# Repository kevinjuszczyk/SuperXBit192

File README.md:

# SuperXBit192
 Lo-fi handheld gaming

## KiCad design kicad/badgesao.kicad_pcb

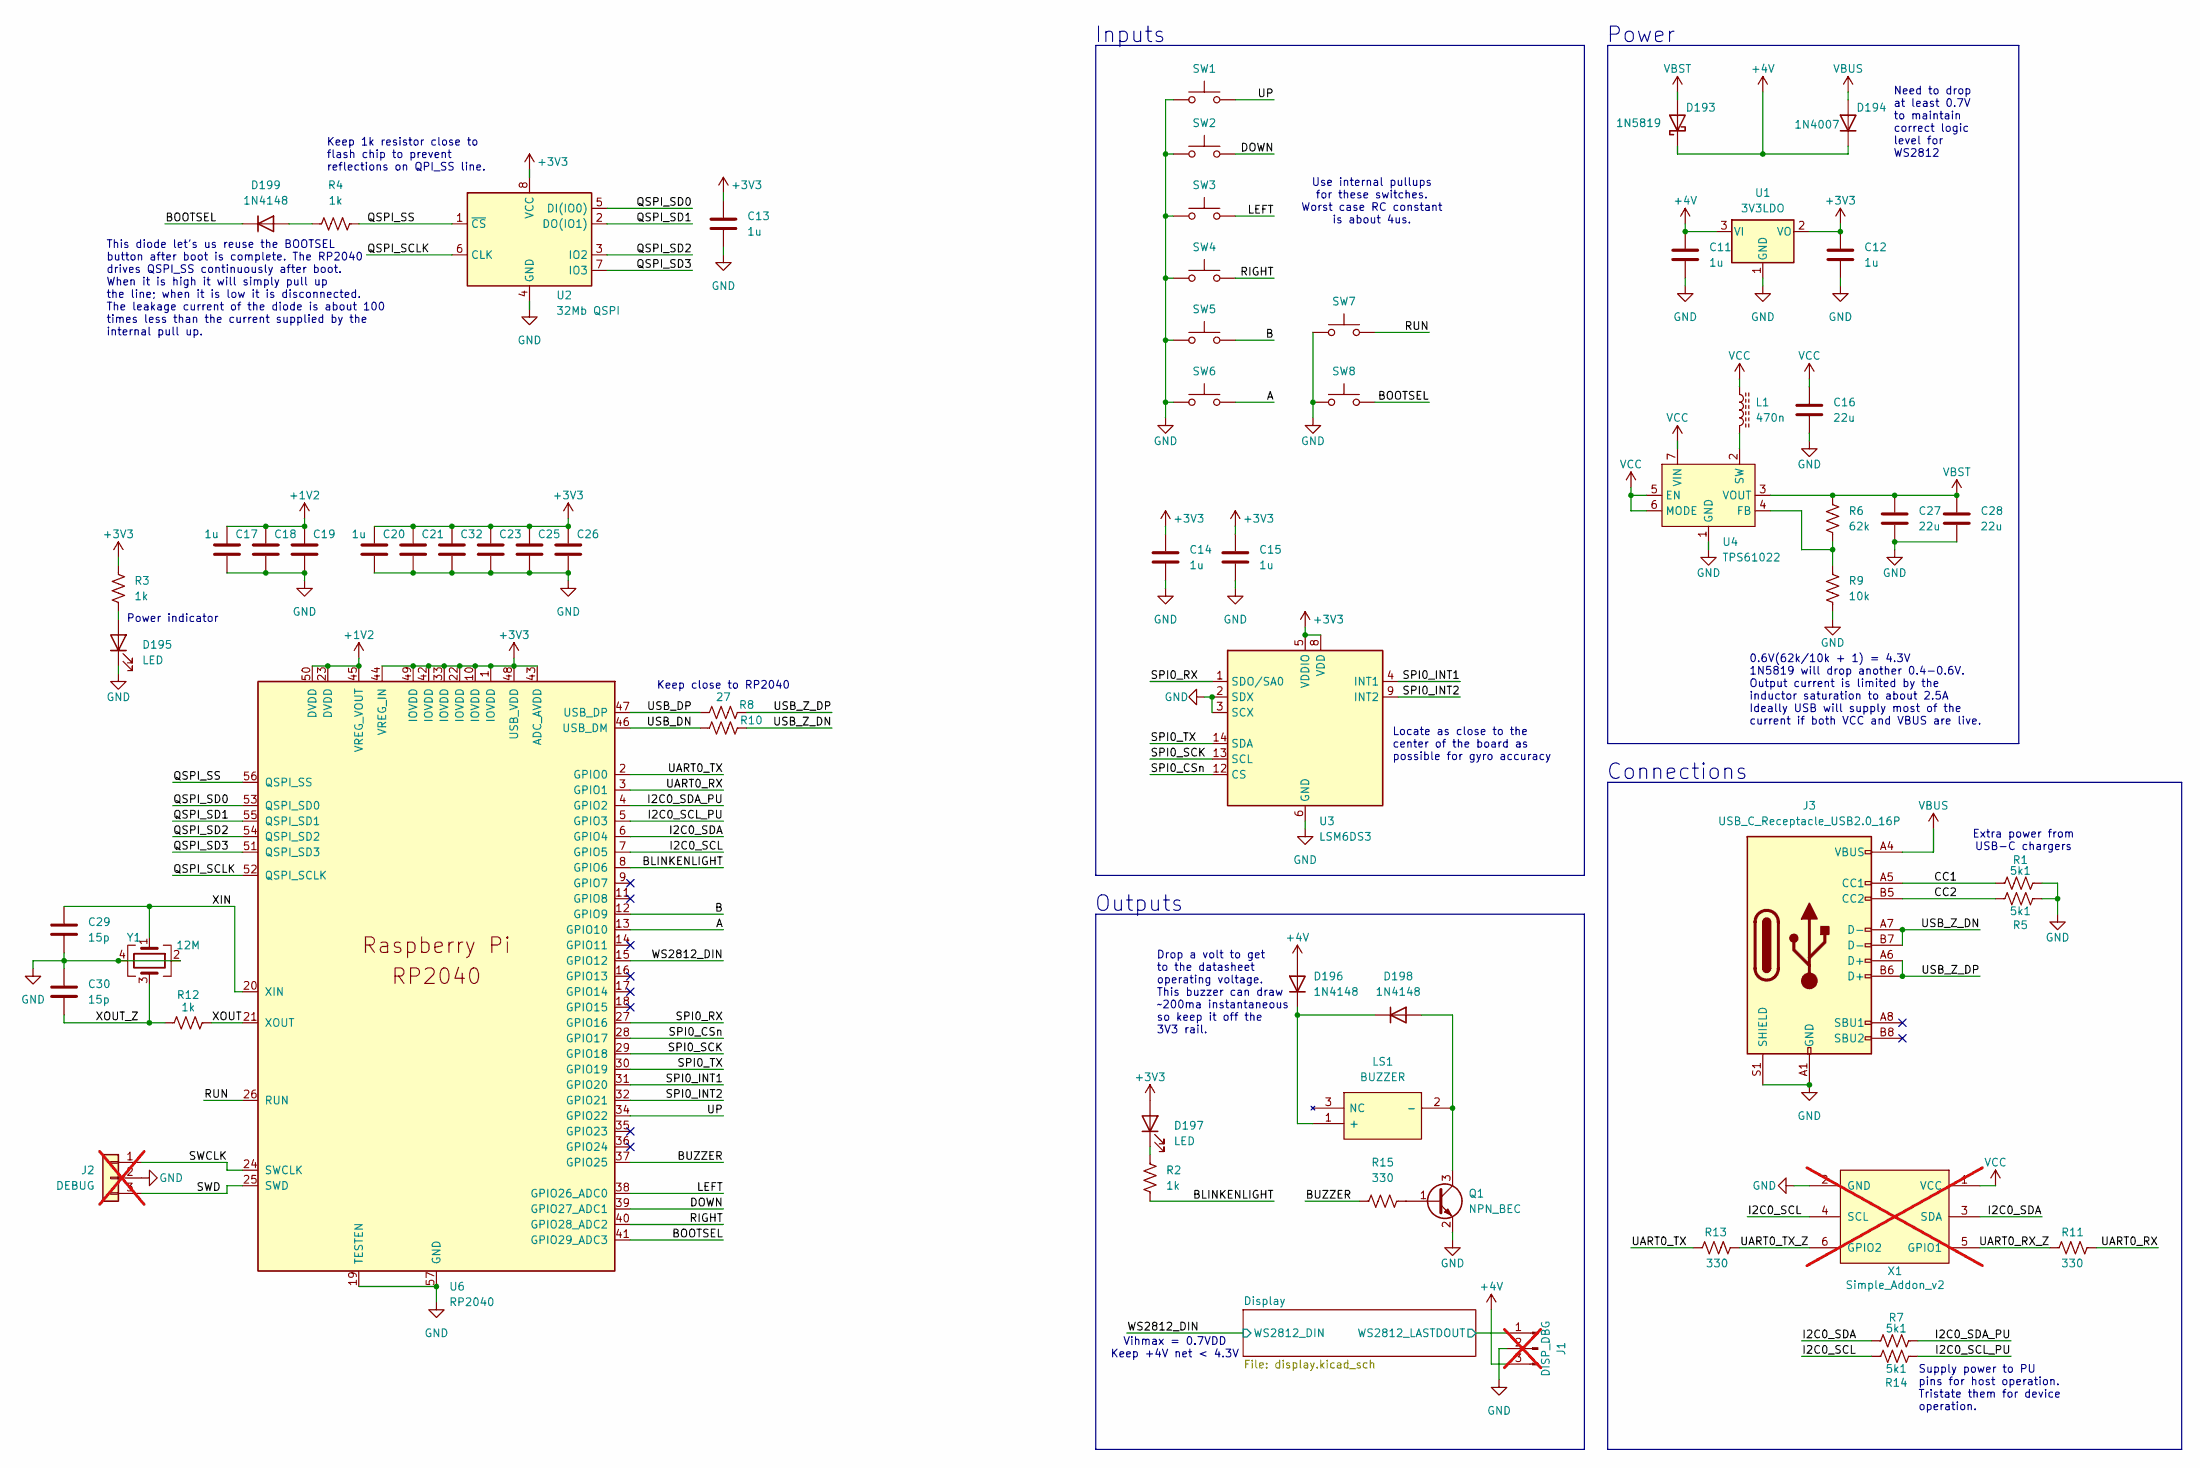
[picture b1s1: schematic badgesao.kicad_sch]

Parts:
C11, C12, C13, C14, C15, C17, C18, C19, C20, C21, C23, C25, C26, C32: 1u; C_0402_1005Metric; Manufacturer_Part_Number CL05A105KA5NQNC; LCSC C52923
C16, C27, C28: 22u; C_0805_2012Metric; Manufacturer_Part_Number CL21A226MAQNNNE; LCSC C45783
C29, C30: 15p; C_0402_1005Metric; Manufacturer_Part_Number 0402CG150J500NT; LCSC C1548
D193: 1N5819; D_SOD-323; Manufacturer_Part_Number 1N5819WS; LCSC C191023
D194: 1N4007; D_SOD-123F; Manufacturer_Part_Number SM4007PL; LCSC C64898
D195, D197: LED; D_0603_1608Metric; Manufacturer_Part_Number KT-0603R; LCSC C2286
D196, D198, D199: 1N4148; D_SOD-523; Manufacturer_Part_Number 1N4148WT; LCSC C7420320
J1: DISP_DBG; PinHeader_1x03_P1.27mm_Vertical; Manufacturer_Part_Number M50-3530342; Digikey_Part 952-3599-ND; not fitted
J2: DEBUG; PinHeader_1x03_P2.54mm_Vertical; Manufacturer_Part_Number 61300311121; Digikey_Part 732-5316-ND; not fitted
J3: USB_C_Receptacle_USB2.0_16P; USB_C_Receptacle_GCT_USB4105-xx-A_16P_TopMnt_Horizontal; Manufacturer_Part_Number U263-163N-4BLS1735; LCSC C2931474
L1: 470n; L_1008_2520Metric; Manufacturer_Part_Number 1239AS-H-R47M=P2; LCSC C576393
LS1: BUZZER; CMT5023SSMTTR; Manufacturer_Part_Number FUET-5020; LCSC C391029
Q1: NPN_BEC; SOT-323_SC-70; Manufacturer_Part_Number MMST3904; LCSC C22388837
R1, R5, R7, R14: 5k1; R_0402_1005Metric; Manufacturer_Part_Number 0402WGF5101TCE; LCSC C25905
R2, R3, R4, R12: 1k; R_0402_1005Metric; Manufacturer_Part_Number 0402WGF1001TCE; LCSC C11702
R6: 62k; R_0402_1005Metric; Manufacturer_Part_Number FRC0402J623TS; LCSC C2929930
R8, R10: 27; R_0402_1005Metric; Manufacturer_Part_Number 0402WGF330JTCE; LCSC C25105
R9: 10k; R_0402_1005Metric; Manufacturer_Part_Number 0402WGF1002TCE; LCSC C25744
R11, R13, R15: 330; R_0402_1005Metric; Manufacturer_Part_Number 0402WGF3300TCE; LCSC C25104
SW1: UP; SW_SPST_PTS810; Manufacturer_Part_Number PTS810SJM250SMTRLFS; LCSC C116501
SW2: DOWN; SW_SPST_PTS810; Manufacturer_Part_Number PTS810SJM250SMTRLFS; LCSC C116501
SW3: LEFT; SW_SPST_PTS810; Manufacturer_Part_Number PTS810SJM250SMTRLFS; LCSC C116501
SW4: RIGHT; SW_SPST_PTS810; Manufacturer_Part_Number PTS810SJM250SMTRLFS; LCSC C116501
SW5: B; SW_SPST_PTS810; Manufacturer_Part_Number PTS810SJM250SMTRLFS; LCSC C116501
SW6: A; SW_SPST_PTS810; Manufacturer_Part_Number PTS810SJM250SMTRLFS; LCSC C116501
SW7: RESET; PTS830GM140SMTRLFS; Manufacturer_Part_Number PTS830GG140SMTRLFS; LCSC C221902
SW8: BOOTSEL; PTS830GM140SMTRLFS; Manufacturer_Part_Number PTS830GG140SMTRLFS; LCSC C221902
U1: 3V3LDO; SOT-23; Manufacturer_Part_Number XC6206P332MR-G; LCSC C5446
U2: 32Mb QSPI; Winbond_USON-8-1EP_3x2mm_P0.5mm_EP0.2x1.6mm; Manufacturer_Part_Number ZD25WQ32CEIGR; LCSC C5258281
U3: LSM6DS3; LGA-14_3x2.5mm_P0.5mm_LayoutBorder3x4y; Manufacturer_Part_Number LSM6DS3TR; LCSC C95230
U4: TPS61022; Texas_RWU0007A_VQFN-7_2x2mm_P0.5mm; Manufacturer_Part_Number TPS61022RWUR; LCSC C915088
U6: RP2040; QFN-56-1EP_7x7mm_P0.4mm_EP3.2x3.2mm; Manufacturer_Part_Number RP2040; LCSC C2040
X1: Simple_Addon_v2; Simple_Addon_v2-SAO-2x3; Manufacturer_Part_Number 75869-131LF; Digikey_Part 609-2845-ND; not fitted
Y1: 12M; Crystal_SMD_SeikoEpson_FA238-4Pin_3.2x2.5mm; Manufacturer_Part_Number X322512MSB4SI; LCSC C9002

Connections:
+1V2: C17.1, C18.1, C19.1, U6.23 (DVDD), U6.45 (VREG_VOUT), U6.50 (DVDD)
+4V: C11.1, D193.1 (K), D194.1 (K), D196.2 (A), J1.3, U1.3 (VI); also elsewhere on the board
/A: SW6.2, U6.13 (GPIO10)
/B: SW5.2, U6.12 (GPIO9)
/BLINKENLIGHT: R2.1, U6.8 (GPIO6)
/CC1: J3.A5 (CC1), R1.2
/CC2: J3.B5 (CC2), R5.2
/Display/WS2812_LASTDOUT: J1.1; also elsewhere on the board
/I2C0_SCL: R14.2, U6.7 (GPIO5), X1.4 (SCL)
/I2C0_SCL_PU: R14.1, U6.5 (GPIO3)
/I2C0_SDA: R7.2, U6.6 (GPIO4), X1.3 (SDA)
/I2C0_SDA_PU: R7.1, U6.4 (GPIO2)
/QSPI_SCLK: U2.6 (CLK), U6.52 (QSPI_SCLK)
/QSPI_SD0: U2.5 (DI(IO0)), U6.53 (QSPI_SD0)
/QSPI_SD1: U2.2 (DO(IO1)), U6.55 (QSPI_SD1)
/QSPI_SD2: U2.3 (IO2), U6.54 (QSPI_SD2)
/QSPI_SD3: U2.7 (IO3), U6.51 (QSPI_SD3)
/QSPI_SS: R4.1, U2.1 (~CS), U6.56 (QSPI_SS)
/RUN: SW7.2, U6.26 (RUN)
/SWCLK: J2.1, U6.24 (SWCLK)
/SWD: J2.3, U6.25 (SWD)
/UART0_RX: R11.2, U6.3 (GPIO1)
/UART0_RX_Z: R11.1, X1.5 (GPIO1)
/UART0_TX: R13.1, U6.2 (GPIO0)
/UART0_TX_Z: R13.2, X1.6 (GPIO2)
/USB_DN: R10.2, U6.46 (USB_DM)
/USB_DP: R8.2, U6.47 (USB_DP)
/USB_Z_DN: J3.A7 (D-), J3.B7 (D-), R10.1
/USB_Z_DP: J3.A6 (D+), J3.B6 (D+), R8.1
/WS2812_DIN: U6.15 (GPIO12); also elsewhere on the board
/XIN: C29.1, U6.20 (XIN), Y1.1
/XOUT: R12.1, U6.21 (XOUT)
/XOUT_Z: C30.2, R12.2, Y1.3
unnamed: D195.2 (A), R3.1
unnamed: D196.1 (K), D198.1 (K), LS1.1 (+)
unnamed: D197.1 (K), R2.2
unnamed: D198.2 (A), LS1.2 (-), Q1.3 (C)
unnamed: D199.2 (A), R4.2
unnamed: Q1.1 (B), R15.1
unnamed: R6.2, R9.1, U4.4 (FB)
unnamed: L1.2, U4.2 (SW)
VBST: C27.1, C28.1, D193.2 (A), R6.1, U4.3 (VOUT)
VBUS: D194.2 (A), J3.A4 (VBUS), J3.A9 (VBUS), J3.B4 (VBUS), J3.B9 (VBUS)
VCC: C16.1, L1.1, U4.5 (EN), U4.6 (MODE), U4.7 (VIN), X1.1 (VCC)

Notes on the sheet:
This diode let's us reuse the BOOTSEL button after boot is complete. The RP2040 drives QSPI_SS continuously after boot. When it is high it will simply pull up the line; when it is low it is disconnected. The leakage current of the diode is about 100 times less than the current supplied by the inter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
0.6V(62k/10k + 1) = 4.3V 1N5819 will drop another 0.4-0.6V. Output current is limited by the inductor saturation to about 2.5A Ideally USB will supply most of the current if both VCC and VBUS are live.
Need to drop at least 0.7V to maintain correct logic level for WS2812
Inputs
Extra power from USB-C chargers
Connections
Drop a volt to get to the datasheet operating voltage. This buzzer can draw ~200ma instantaneous so keep it off the 3V3 rail.
Power
Supply power to PU pins for host operation. Tristate them for device operation.
Outputs
Power indicator
Vihmax = 0.7VDD Keep +4V net < 4.3V
Keep 1k resistor close to flash chip to prevent reflections on QPI_SS line.
Use internal pullups for these switches. Worst case RC constant is about 4us.
Keep close to RP2040
Locate as close to the center of the board as possible for gyro accuracy

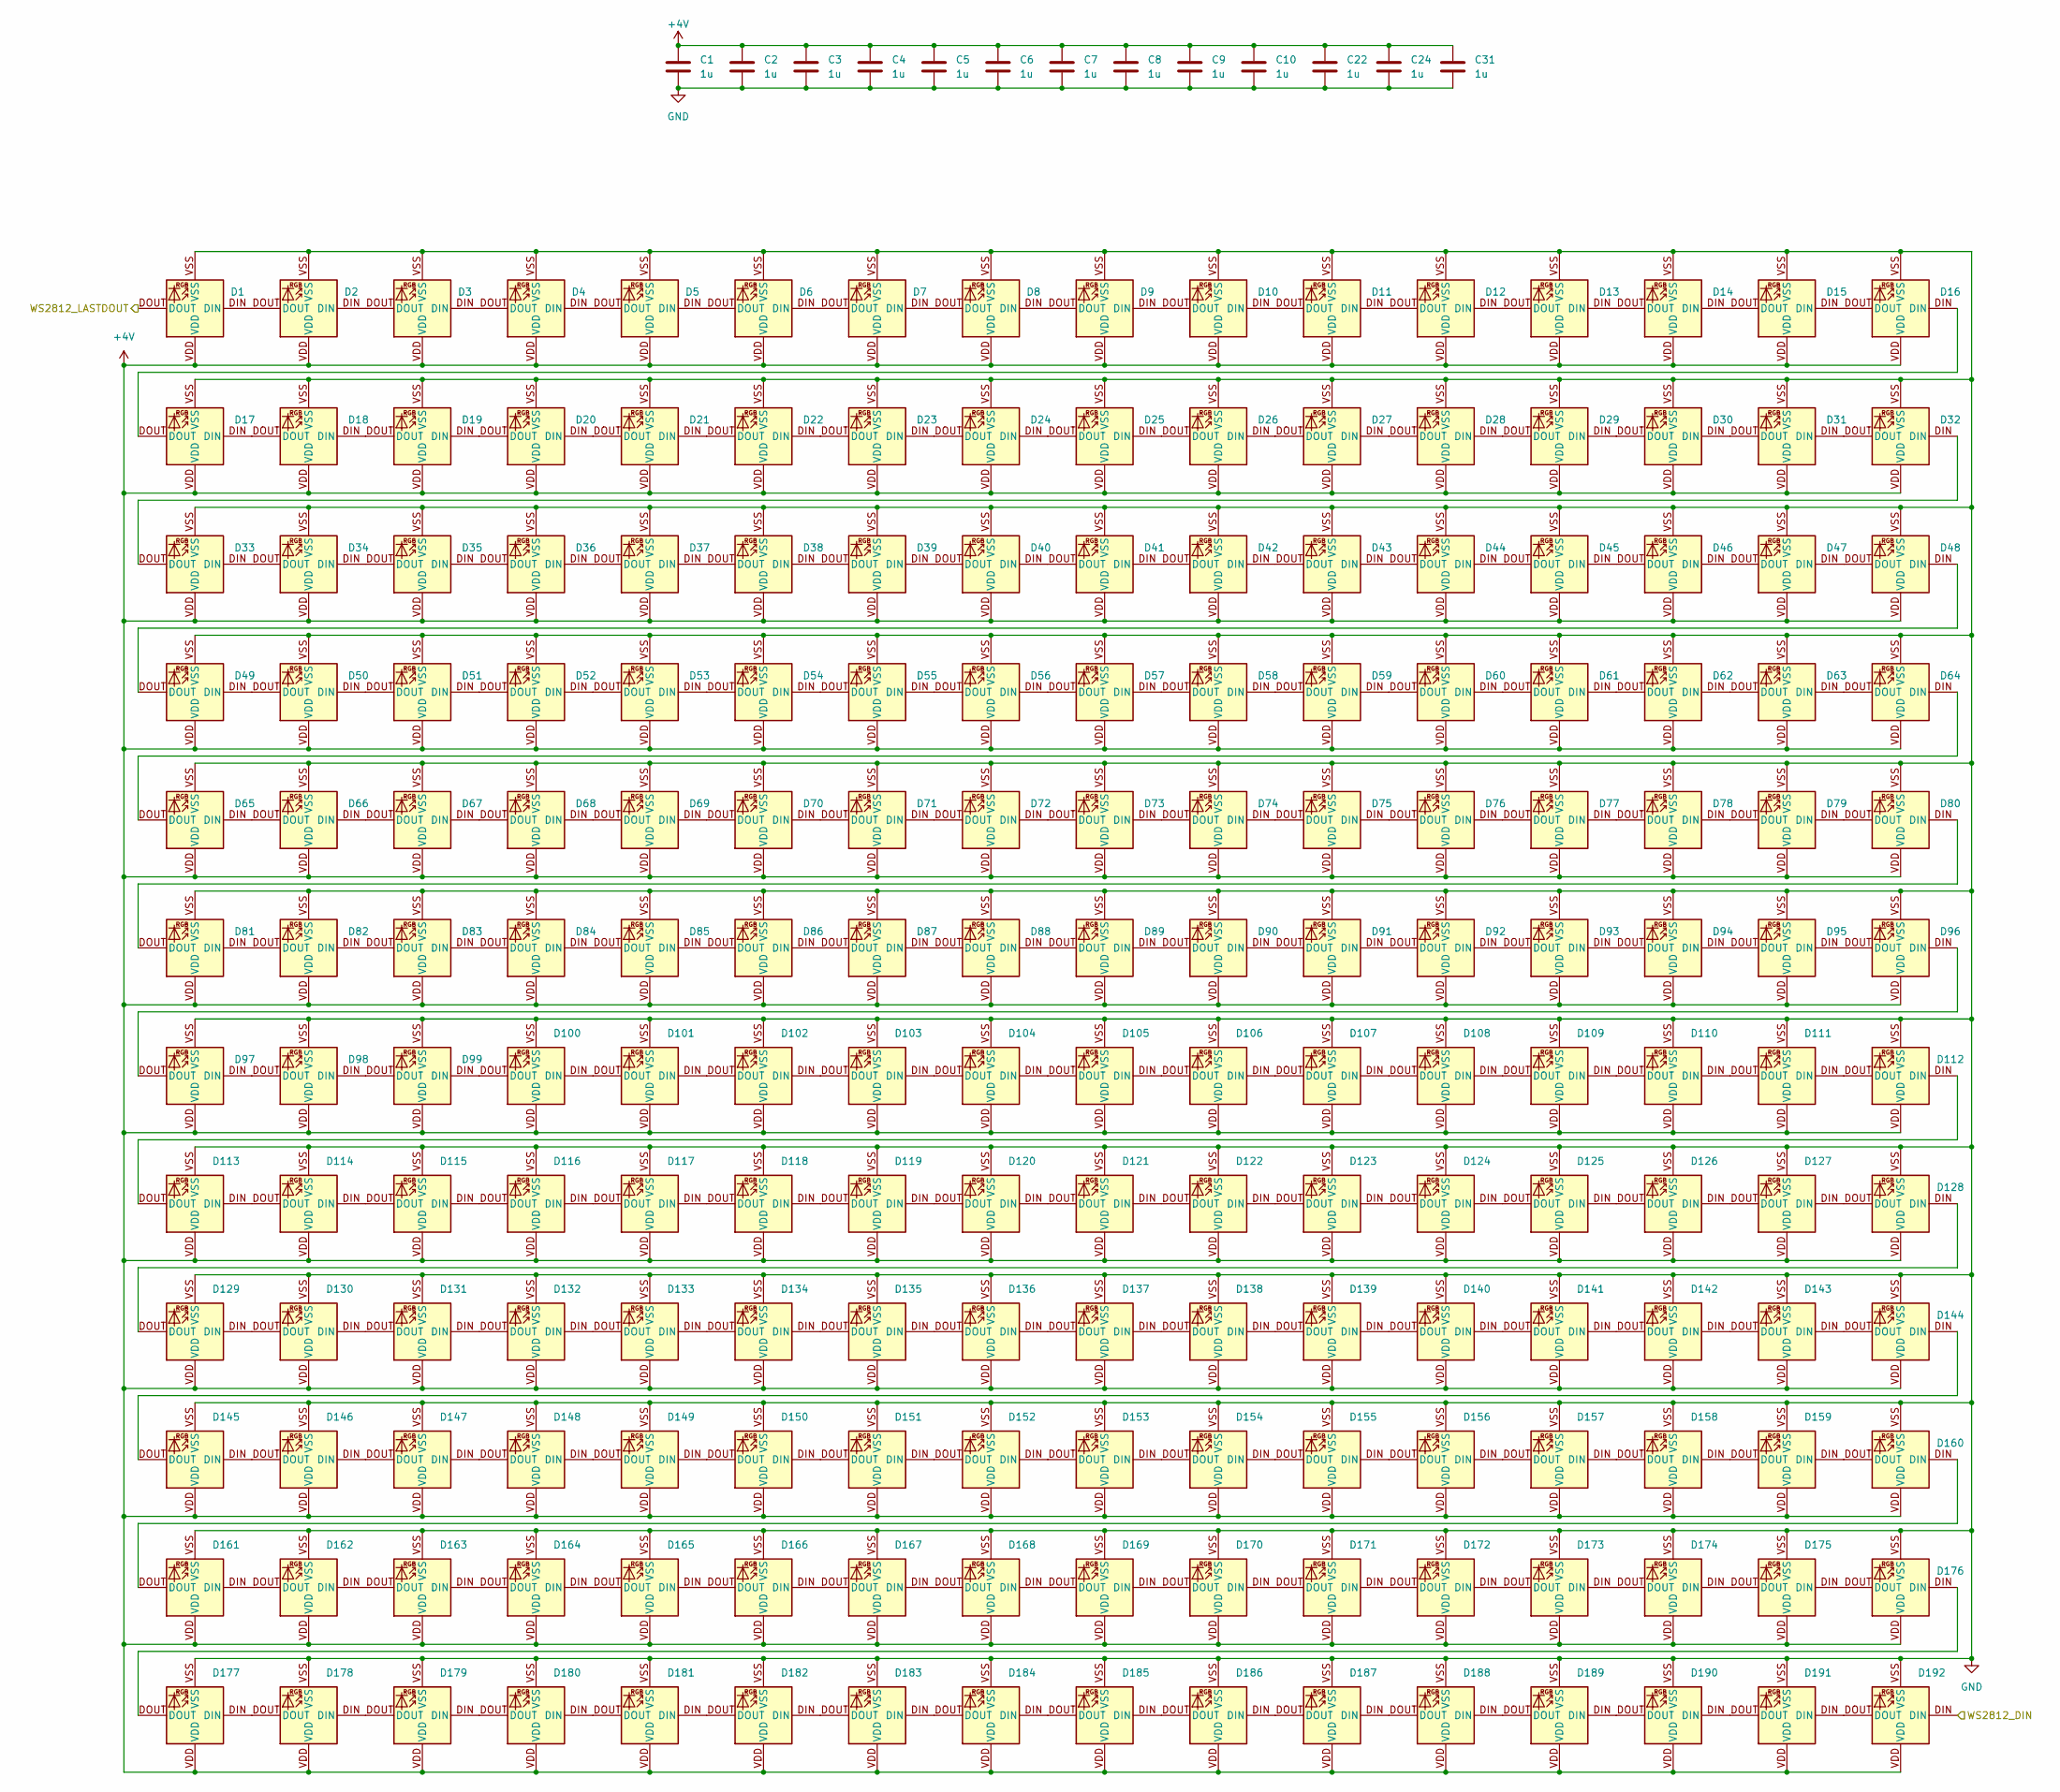
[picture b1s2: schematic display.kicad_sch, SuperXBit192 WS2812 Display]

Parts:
C1, C2, C3, C4, C5, C6, C7, C8, C9, C10, C22, C24, C31: 1u; C_0402_1005Metric; Manufacturer_Part_Number CL05A105KA5NQNC; LCSC C52923
D1, D2, D3, D4, D5, D6, D7, D8, D9, D10, D11, D12, D13, D14, D15, D16, D17, D18, D19, D20, D21, D22, D23, D24, D25, D26, D27, D28, D29, D30, D31, D32, D33, D34, D35, D36, D37, D38, D39, D40, D41, D42, D43, D44, D45, D46, D47, D48, D49, D50, D51, D52, D53, D54, D55, D56, D57, D58, D59, D60, D61, D62, D63, D64, D65, D66, D67, D68, D69, D70, D71, D72, D73, D74, D75, D76, D77, D78, D79, D80, D81, D82, D83, D84, D85, D86, D87, D88, D89, D90, D91, D92, D93, D94, D95, D96, D97, D98, D99, D100, D101, D102, D103, D104, D105, D106, D107, D108, D109, D110, D111, D112, D113, D114, D115, D116, D117, D118, D119, D120, D121, D122, D123, D124, D125, D126, D127, D128, D129, D130, D131, D132, D133, D134, D135, D136, D137, D138, D139, D140, D141, D142, D143, D144, D145, D146, D147, D148, D149, D150, D151, D152, D153, D154, D155, D156, D157, D158, D159, D160, D161, D162, D163, D164, D165, D166, D167, D168, D169, D170, D171, D172, D173, D174, D175, D176, D177, D178, D179, D180, D181, D182, D183, D184, D185, D186, D187, D188, D189, D190, D191, D192: WS2812B; LED_WS2812B-1615_PLCC4_1.6x1.5mm; Manufacturer_Part_Number XL-1615RGBC-WS2812B; LCSC C5349954

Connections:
+4V: C1.1, C2.1, C3.1, C4.1, C5.1, C6.1, C7.1, C8.1, C9.1, C10.1, C22.1, C24.1, C31.1, D1.VDD, D2.VDD, D3.VDD, D4.VDD, D5.VDD, D6.VDD, D7.VDD, D8.VDD, D9.VDD, D10.VDD, D11.VDD, D12.VDD, D13.VDD, D14.VDD, D15.VDD, D16.VDD, D17.VDD, D18.VDD, D19.VDD, D20.VDD, D21.VDD, D22.VDD, D23.VDD, D24.VDD, D25.VDD, D26.VDD, D27.VDD, D28.VDD, D29.VDD, D30.VDD, D31.VDD, D32.VDD, D33.VDD, D34.VDD, D35.VDD, D36.VDD, D37.VDD, D38.VDD, D39.VDD, D40.VDD, D41.VDD, D42.VDD, D43.VDD, D44.VDD, D45.VDD, D46.VDD, D47.VDD, D48.VDD, D49.VDD, D50.VDD, D51.VDD, D52.VDD, D53.VDD, D54.VDD, D55.VDD, D56.VDD, D57.VDD, D58.VDD, D59.VDD, D60.VDD, D61.VDD, D62.VDD, D63.VDD, D64.VDD, D65.VDD, D66.VDD, D67.VDD, D68.VDD, D69.VDD, D70.VDD, D71.VDD, D72.VDD, D73.VDD, D74.VDD, D75.VDD, D76.VDD, D77.VDD, D78.VDD, D79.VDD, D80.VDD, D81.VDD, D82.VDD, D83.VDD, D84.VDD, D85.VDD, D86.VDD, D87.VDD, D88.VDD, D89.VDD, D90.VDD, D91.VDD, D92.VDD, D93.VDD, D94.VDD, D95.VDD, D96.VDD, D97.VDD, D98.VDD, D99.VDD, D100.VDD, D101.VDD, D102.VDD, D103.VDD, D104.VDD, D105.VDD, D106.VDD, D107.VDD, D108.VDD, D109.VDD, D110.VDD, D111.VDD, D112.VDD, D113.VDD, D114.VDD, D115.VDD, D116.VDD, D117.VDD, D118.VDD, D119.VDD, D120.VDD, D121.VDD, D122.VDD, D123.VDD, D124.VDD, D125.VDD, D126.VDD, D127.VDD, D128.VDD, D129.VDD, D130.VDD, D131.VDD, D132.VDD, D133.VDD, D134.VDD, D135.VDD, D136.VDD, D137.VDD, D138.VDD, D139.VDD, D140.VDD, D141.VDD, D142.VDD, D143.VDD, D144.VDD, D145.VDD, D146.VDD, D147.VDD, D148.VDD, D149.VDD, D150.VDD, D151.VDD, D152.VDD, D153.VDD, D154.VDD, D155.VDD, D156.VDD, D157.VDD, D158.VDD, D159.VDD, D160.VDD, D161.VDD, D162.VDD, D163.VDD, D164.VDD, D165.VDD, D166.VDD, D167.VDD, D168.VDD, D169.VDD, D170.VDD, D171.VDD, D172.VDD, D173.VDD, D174.VDD, D175.VDD, D176.VDD, D177.VDD, D178.VDD, D179.VDD, D180.VDD, D181.VDD, D182.VDD, D183.VDD, D184.VDD, D185.VDD, D186.VDD, D187.VDD, D188.VDD, D189.VDD, D190.VDD, D191.VDD, D192.VDD; also elsewhere on the board
/Display/WS2812_LASTDOUT: D1.DOUT; also elsewhere on the board
/WS2812_DIN: D192.DIN; also elsewhere on the board
unnamed: D1.DIN, D2.DOUT
unnamed: D2.DIN, D3.DOUT
unnamed: D3.DIN, D4.DOUT
unnamed: D4.DIN, D5.DOUT
unnamed: D5.DIN, D6.DOUT
unnamed: D6.DIN, D7.DOUT
unnamed: D7.DIN, D8.DOUT
unnamed: D8.DIN, D9.DOUT
unnamed: D10.DIN, D11.DOUT
unnamed: D9.DIN, D10.DOUT
unnamed: D11.DIN, D12.DOUT
unnamed: D12.DIN, D13.DOUT
unnamed: D13.DIN, D14.DOUT
unnamed: D14.DIN, D15.DOUT
unnamed: D15.DIN, D16.DOUT
unnamed: D16.DIN, D17.DOUT
unnamed: D17.DIN, D18.DOUT
unnamed: D18.DIN, D19.DOUT
unnamed: D19.DIN, D20.DOUT
unnamed: D20.DIN, D21.DOUT
unnamed: D21.DIN, D22.DOUT
unnamed: D22.DIN, D23.DOUT
unnamed: D23.DIN, D24.DOUT
unnamed: D24.DIN, D25.DOUT
unnamed: D25.DIN, D26.DOUT
unnamed: D26.DIN, D27.DOUT
unnamed: D27.DIN, D28.DOUT
unnamed: D28.DIN, D29.DOUT
unnamed: D29.DIN, D30.DOUT
unnamed: D30.DIN, D31.DOUT
unnamed: D31.DIN, D32.DOUT
unnamed: D32.DIN, D33.DOUT
unnamed: D33.DIN, D34.DOUT
unnamed: D34.DIN, D35.DOUT
unnamed: D35.DIN, D36.DOUT
unnamed: D36.DIN, D37.DOUT
unnamed: D37.DIN, D38.DOUT
unnamed: D38.DIN, D39.DOUT
unnamed: D39.DIN, D40.DOUT
unnamed: D40.DIN, D41.DOUT
unnamed: D41.DIN, D42.DOUT
unnamed: D42.DIN, D43.DOUT
unnamed: D43.DIN, D44.DOUT
unnamed: D44.DIN, D45.DOUT
unnamed: D45.DIN, D46.DOUT
unnamed: D46.DIN, D47.DOUT
unnamed: D47.DIN, D48.DOUT
unnamed: D48.DIN, D49.DOUT
unnamed: D49.DIN, D50.DOUT
unnamed: D50.DIN, D51.DOUT
unnamed: D51.DIN, D52.DOUT
unnamed: D52.DIN, D53.DOUT
unnamed: D53.DIN, D54.DOUT
unnamed: D54.DIN, D55.DOUT
unnamed: D55.DIN, D56.DOUT
unnamed: D56.DIN, D57.DOUT
unnamed: D57.DIN, D58.DOUT
unnamed: D58.DIN, D59.DOUT
unnamed: D59.DIN, D60.DOUT
unnamed: D60.DIN, D61.DOUT
unnamed: D61.DIN, D62.DOUT
unnamed: D62.DIN, D63.DOUT
unnamed: D63.DIN, D64.DOUT
unnamed: D64.DIN, D65.DOUT
unnamed: D65.DIN, D66.DOUT
unnamed: D66.DIN, D67.DOUT
unnamed: D67.DIN, D68.DOUT
unnamed: D68.DIN, D69.DOUT
unnamed: D69.DIN, D70.DOUT
unnamed: D70.DIN, D71.DOUT
unnamed: D71.DIN, D72.DOUT
unnamed: D72.DIN, D73.DOUT
unnamed: D73.DIN, D74.DOUT
unnamed: D74.DIN, D75.DOUT
unnamed: D75.DIN, D76.DOUT
unnamed: D76.DIN, D77.DOUT
unnamed: D77.DIN, D78.DOUT
unnamed: D78.DIN, D79.DOUT
unnamed: D79.DIN, D80.DOUT
unnamed: D80.DIN, D81.DOUT
unnamed: D81.DIN, D82.DOUT
unnamed: D82.DIN, D83.DOUT
unnamed: D83.DIN, D84.DOUT
unnamed: D84.DIN, D85.DOUT
unnamed: D85.DIN, D86.DOUT
unnamed: D86.DIN, D87.DOUT
unnamed: D87.DIN, D88.DOUT
unnamed: D88.DIN, D89.DOUT
unnamed: D89.DIN, D90.DOUT
unnamed: D90.DIN, D91.DOUT
unnamed: D91.DIN, D92.DOUT
unnamed: D92.DIN, D93.DOUT
unnamed: D93.DIN, D94.DOUT
unnamed: D94.DIN, D95.DOUT
unnamed: D95.DIN, D96.DOUT
unnamed: D96.DIN, D97.DOUT
unnamed: D97.DIN, D98.DOUT
unnamed: D98.DIN, D99.DOUT
unnamed: D100.DIN, D101.DOUT
unnamed: D99.DIN, D100.DOUT
unnamed: D101.DIN, D102.DOUT
unnamed: D102.DIN, D103.DOUT
unnamed: D103.DIN, D104.DOUT
unnamed: D104.DIN, D105.DOUT
unnamed: D105.DIN, D106.DOUT
unnamed: D106.DIN, D107.DOUT
unnamed: D107.DIN, D108.DOUT
unnamed: D108.DIN, D109.DOUT
unnamed: D109.DIN, D110.DOUT
unnamed: D110.DIN, D111.DOUT
unnamed: D111.DIN, D112.DOUT
unnamed: D112.DIN, D113.DOUT
unnamed: D113.DIN, D114.DOUT
unnamed: D114.DIN, D115.DOUT
unnamed: D115.DIN, D116.DOUT
unnamed: D116.DIN, D117.DOUT
unnamed: D117.DIN, D118.DOUT
unnamed: D118.DIN, D119.DOUT
unnamed: D119.DIN, D120.DOUT
unnamed: D120.DIN, D121.DOUT
unnamed: D121.DIN, D122.DOUT
unnamed: D122.DIN, D123.DOUT
unnamed: D123.DIN, D124.DOUT
unnamed: D124.DIN, D125.DOUT
unnamed: D125.DIN, D126.DOUT
unnamed: D126.DIN, D127.DOUT
unnamed: D127.DIN, D128.DOUT
unnamed: D128.DIN, D129.DOUT
unnamed: D129.DIN, D130.DOUT
unnamed: D130.DIN, D131.DOUT
unnamed: D131.DIN, D132.DOUT
unnamed: D132.DIN, D133.DOUT
unnamed: D133.DIN, D134.DOUT
unnamed: D134.DIN, D135.DOUT
unnamed: D135.DIN, D136.DOUT
unnamed: D136.DIN, D137.DOUT
unnamed: D137.DIN, D138.DOUT
unnamed: D138.DIN, D139.DOUT
unnamed: D139.DIN, D140.DOUT
unnamed: D140.DIN, D141.DOUT
unnamed: D141.DIN, D142.DOUT
unnamed: D142.DIN, D143.DOUT
unnamed: D143.DIN, D144.DOUT
unnamed: D144.DIN, D145.DOUT
unnamed: D145.DIN, D146.DOUT
unnamed: D146.DIN, D147.DOUT
unnamed: D147.DIN, D148.DOUT
unnamed: D148.DIN, D149.DOUT
unnamed: D149.DIN, D150.DOUT
unnamed: D150.DIN, D151.DOUT
unnamed: D151.DIN, D152.DOUT
unnamed: D152.DIN, D153.DOUT
unnamed: D153.DIN, D154.DOUT
unnamed: D154.DIN, D155.DOUT
unnamed: D155.DIN, D156.DOUT
unnamed: D156.DIN, D157.DOUT
unnamed: D157.DIN, D158.DOUT
unnamed: D158.DIN, D159.DOUT
unnamed: D159.DIN, D160.DOUT
unnamed: D160.DIN, D161.DOUT
unnamed: D161.DIN, D162.DOUT
unnamed: D162.DIN, D163.DOUT
unnamed: D163.DIN, D164.DOUT
unnamed: D164.DIN, D165.DOUT
unnamed: D165.DIN, D166.DOUT
unnamed: D166.DIN, D167.DOUT
unnamed: D167.DIN, D168.DOUT
unnamed: D168.DIN, D169.DOUT
unnamed: D169.DIN, D170.DOUT
unnamed: D170.DIN, D171.DOUT
unnamed: D171.DIN, D172.DOUT
unnamed: D172.DIN, D173.DOUT
unnamed: D173.DIN, D174.DOUT
unnamed: D174.DIN, D175.DOUT
unnamed: D175.DIN, D176.DOUT
unnamed: D176.DIN, D177.DOUT
unnamed: D177.DIN, D178.DOUT
unnamed: D178.DIN, D179.DOUT
unnamed: D179.DIN, D180.DOUT
unnamed: D180.DIN, D181.DOUT
unnamed: D181.DIN, D182.DOUT
unnamed: D182.DIN, D183.DOUT
unnamed: D183.DIN, D184.DOUT
unnamed: D184.DIN, D185.DOUT
unnamed: D185.DIN, D186.DOUT
unnamed: D186.DIN, D187.DOUT
unnamed: D187.DIN, D188.DOUT
unnamed: D188.DIN, D189.DOUT
unnamed: D189.DIN, D190.DOUT
unnamed: D190.DIN, D191.DOUT
unnamed: D191.DIN, D192.DOUT

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
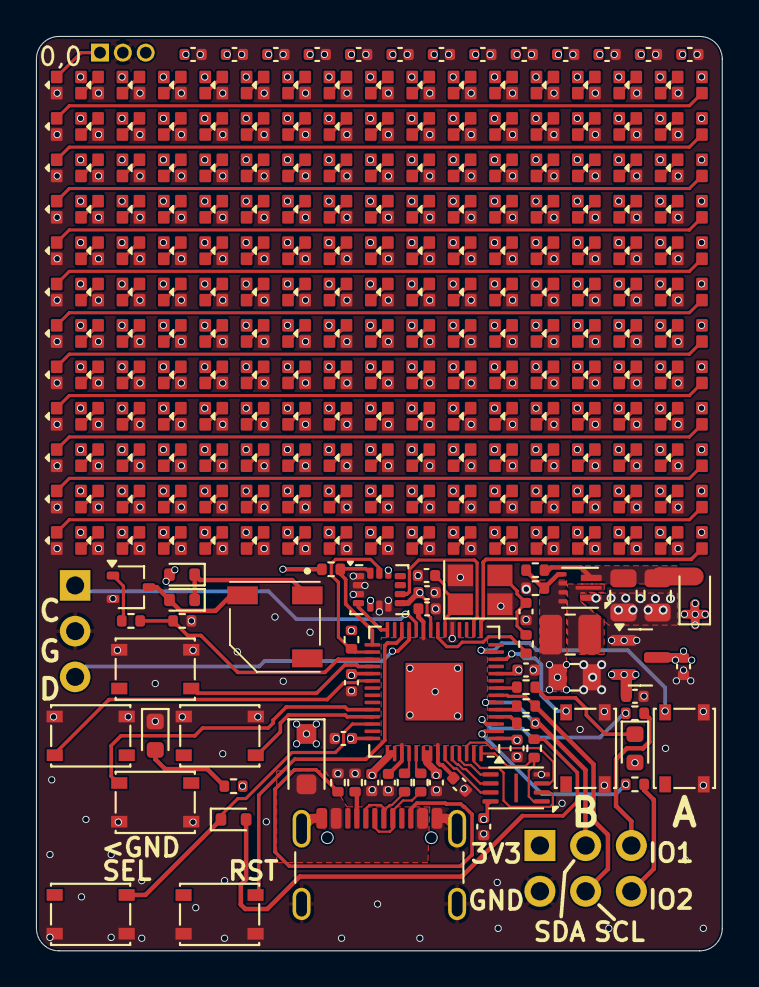
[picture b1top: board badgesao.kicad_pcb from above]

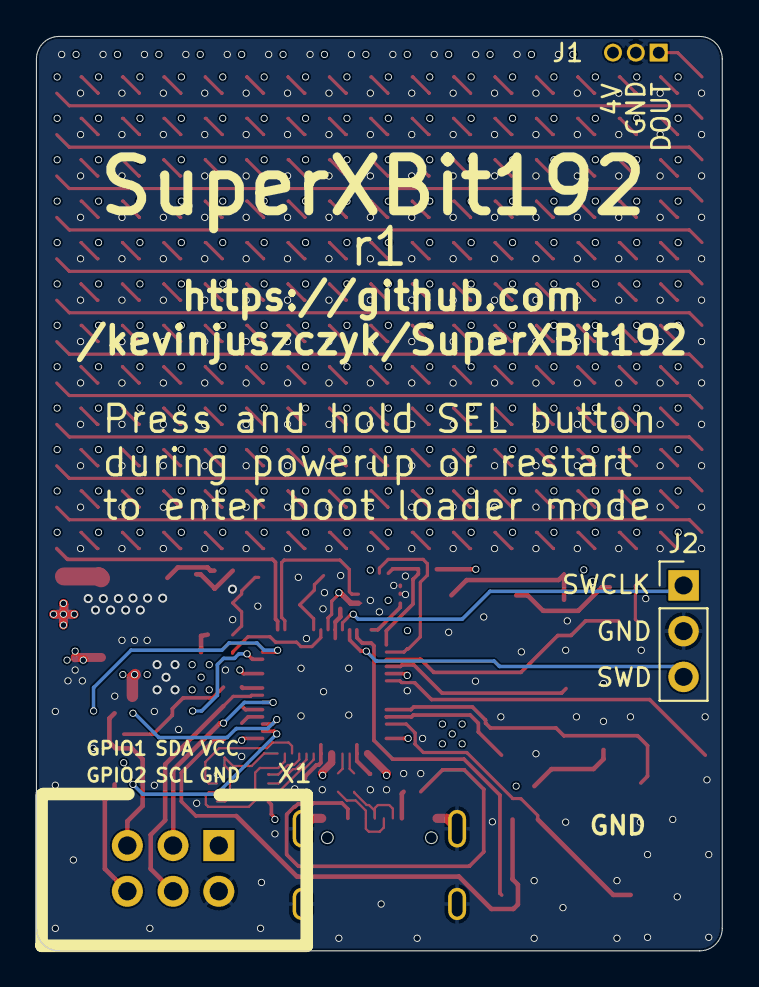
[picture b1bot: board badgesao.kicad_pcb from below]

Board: 6 copper layers, 38.1 x 50.8 mm, 269 parts (2 on the bottom side), 247 nets.

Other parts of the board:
R16: 1k; R_0402_1005Metric
R17, R18: 5k1; R_0402_1005Metric

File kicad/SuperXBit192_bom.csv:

"Reference","Value","Datasheet","Footprint","Qty","DNP","LCSC","Manufacturer_Name","Manufacturer_Part_Number","Digikey_Part"
"C1,C2,C3,C4,C5,C6,C7,C8,C9,C10,C11,C12,C13,C15,C17,C18,C19,C20,C21,C22,C23,C24,C25,C26,C31,C32","1u","https://wmsc.lcsc.com/wmsc/upload/file/pdf/v2/lcsc/230414003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","Capacitor_SMD:C_0402_1005Metric","26","","C52923","Samsung Electro-Mechanics","CL05A105KA5NQNC","1276-1445-1-ND"
"C16,C27,C28","22u","https://wmsc.lcsc.com/wmsc/upload/file/pdf/v2/lcsc/230414003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","Capacitor_SMD:C_0805_2012Metric","3","","C45783","Samsung Electro-Mechanics","CL21A226MAQNNNE","1276-2908-1-ND"
"C29,C30","15p","https://wmsc.lcsc.com/wmsc/upload/file/pdf/v2/lcsc/230414003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","Capacitor_SMD:C_0402_1005Metric","2","","C1548","FH (Guangdong Fenghua Advanced Tech)","0402CG150J500NT","490-5888-1-ND"
"D1,D2,D3,D4,D5,D6,D7,D8,D9,D10,D11,D12,D13,D14,D15,D16,D17,D18,D19,D20,D21,D22,D23,D24,D25,D26,D27,D28,D29,D30,D31,D32,D33,D34,D35,D36,D37,D38,D39,D40,D41,D42,D43,D44,D45,D46,D47,D48,D49,D50,D51,D52,D53,D54,D55,D56,D57,D58,D59,D60,D61,D62,D63,D64,D65,D66,D67,D68,D69,D70,D71,D72,D73,D74,D75,D76,D77,D78,D79,D80,D81,D82,D83,D84,D85,D86,D87,D88,D89,D90,D91,D92,D93,D94,D95,D96,D97,D98,D99,D100,D101,D102,D103,D104,D105,D106,D107,D108,D109,D110,D111,D112,D113,D114,D115,D116,D117,D118,D119,D120,D121,D122,D123,D124,D125,D126,D127,D128,D129,D130,D131,D132,D133,D134,D135,D136,D137,D138,D139,D140,D141,D142,D143,D144,D145,D146,D147,D148,D149,D150,D151,D152,D153,D154,D155,D156,D157,D158,D159,D160,D161,D162,D163,D164,D165,D166,D167,D168,D169,D170,D171,D172,D173,D174,D175,D176,D177,D178,D179,D180,D181,D182,D183,D184,D185,D186,D187,D188,D189,D190,D191,D192","WS2812B","https://wmsc.lcsc.com/wmsc/upload/file/pdf/v2/lcsc/240218150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","kmj_custom:LED_WS2812B-1615_PLCC4_1.6x1.5mm","192","","C5349954","XINGLIGHT","XL-1615RGBC-WS2812B",""
"D193","1N5819","https://wmsc.lcsc.com/wmsc/upload/file/pdf/v2/lcsc/220428143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","Diode_SMD:D_SOD-323","1","","C191023","Guangdong Hottech","1N5819WS","5272-B5819WSCT-ND"
"D194","1N4007","https://wmsc.lcsc.com/wmsc/upload/file/pdf/v2/lcsc/240710112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","Diode_SMD:D_SOD-123F","1","","C64898","MDD(Microdiode Semiconductor)","SM4007PL","SM4007PL-TPMSCT-ND"
"D195,D197","LED","https://wmsc.lcsc.com/wmsc/upload/file/pdf/v2/lcsc/181023111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","Diode_SMD:D_0603_1608Metric","2","","C2286","Hubei KENTO Elec","KT-0603R","3147-B1931USD-20D000814U1930CT-ND"
"D196,D198,D199","1N4148","https://wmsc.lcsc.com/wmsc/upload/file/pdf/v2/lcsc/231117111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","Diode_SMD:D_SOD-523","3","","C7420320","hongjiacheng","1N4148WT","1N4148WTCT-ND"
"J1","DISP_DBG","https://cdn.harwin.com/pdfs/M50-353.pdf","kmj_custom:PinHeader_1x03_P1.27mm_Vertical","1","DNP","C6658360","Harwin","M50-3530342","952-3599-ND"
"J2","DEBUG","https://www.we-online.com/components/products/datasheet/6130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","Connector_PinHeader_2.54mm:PinHeader_1x03_P2.54mm_Vertical","1","DNP","C2915006","WÜRTH ELEKTRONIK","61300311121","732-5316-ND"
"J3","USB_C_Receptacle_USB2.0_16P","https://wmsc.lcsc.com/wmsc/upload/file/pdf/v2/lcsc/220112150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","Connector_USB:USB_C_Receptacle_GCT_USB4105-xx-A_16P_TopMnt_Horizontal","1","","C2931474","XKB Connection","U263-163N-4BLS1735","2073-USB4105-GF-ACT-ND"
"L1","470n","https://wmsc.lcsc.com/wmsc/upload/file/pdf/v2/lcsc/230811154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","Inductor_SMD:L_1008_2520Metric","1","","C576393","Murata Electronics","1239AS-H-R47M=P2","490-10571-1-ND"
"LS1","BUZZER","https://wmsc.lcsc.com/wmsc/upload/file/pdf/v2/lcsc/191211143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","kmj_custom:CMT5023SSMTTR","1","","C391029","FUET","FUET-5020","102-3743-1-ND"
"Q1","NPN_BEC","https://wmsc.lcsc.com/wmsc/upload/file/pdf/v2/lcsc/240426120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","Package_TO_SOT_SMD:SOT-323_SC-70","1","","C22388837","hongjiacheng","MMST3904","4786-MMST3904CT-ND"
"R1,R5,R7,R14,R17,R18","5k1","https://wmsc.lcsc.com/wmsc/upload/file/pdf/v2/lcsc/220601004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","Resistor_SMD:R_0402_1005Metric","6","","C25905","UNI-ROYAL(Uniroyal Elec)","0402WGF5101TCE","P5.10KLCT-ND"
"R2,R3,R4,R12,R16","1k","https://wmsc.lcsc.com/wmsc/upload/file/pdf/v2/lcsc/220601021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","Resistor_SMD:R_0402_1005Metric","5","","C11702","UNI-ROYAL(Uniroyal Elec)","0402WGF1001TCE","311-1.0KJRCT-ND"
"R6","200k","https://wmsc.lcsc.com/wmsc/upload/file/pdf/v2/lcsc/230824100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","Resistor_SMD:R_0402_1005Metric","1","","C25764","UNI-ROYAL(Uniroyal Elec)","0402WGF2003TCE","RMCF0402FT200KCT-ND"
"R8,R10","33","https://wmsc.lcsc.com/wmsc/upload/file/pdf/v2/lcsc/220531190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","Resistor_SMD:R_0402_1005Metric","2","","C25105","UNI-ROYAL(Uniroyal Elec)","0402WGF330JTCE","P33.0LCT-ND"
"R9","33k","https://wmsc.lcsc.com/wmsc/upload/file/pdf/v2/lcsc/220601010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","Resistor_SMD:R_0402_1005Metric","1","","C25779","UNI-ROYAL(Uniroyal Elec)","0402WGF3302TCE","A129645CT-ND"
"R11,R13,R15","330","https://wmsc.lcsc.com/wmsc/upload/file/pdf/v2/lcsc/220531190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","Resistor_SMD:R_0402_1005Metric","3","","C25104","UNI-ROYAL(Uniroyal Elec)","0402WGF3300TCE","311-330LRCT-ND"
"SW1","UP","https://www.lcsc.com/datasheet/lcsc_datasheet_2106070033_C-K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","kmj_custom:SW_SPST_PTS810","1","","C2689510","C&K","PTS815SJM250SMTRLFS","CKN12215-1-ND"
"SW2","DOWN","https://www.lcsc.com/datasheet/lcsc_datasheet_2106070033_C-K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","kmj_custom:SW_SPST_PTS810","1","","C2689510","C&K","PTS815SJM250SMTRLFS","CKN12215-1-ND"
"SW3","LEFT","https://www.lcsc.com/datasheet/lcsc_datasheet_2106070033_C-K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","kmj_custom:SW_SPST_PTS810","1","","C2689510","C&K","PTS815SJM250SMTRLFS","CKN12215-1-ND"
"SW4","RIGHT","https://www.lcsc.com/datasheet/lcsc_datasheet_2106070033_C-K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","kmj_custom:SW_SPST_PTS810","1","","C2689510","C&K","PTS815SJM250SMTRLFS","CKN12215-1-ND"
"SW5","B","https://www.lcsc.com/datasheet/lcsc_datasheet_2106070033_C-K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","kmj_custom:SW_SPST_PTS810","1","","C2689510","C&K","PTS815SJM250SMTRLFS","CKN12215-1-ND"
"SW6","A","https://www.lcsc.com/datasheet/lcsc_datasheet_2106070033_C-K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","kmj_custom:SW_SPST_PTS810","1","","C2689510","C&K","PTS815SJM250SMTRLFS","CKN12215-1-ND"
"SW7","RESET","https://www.lcsc.com/datasheet/lcsc_datasheet_2106070033_C-K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","kmj_custom:SW_SPST_PTS810","1","","C2689510","C&K","PTS815SJM250SMTRLFS","CKN12215-1-ND"
"SW8","BOOTSEL","https://www.lcsc.com/datasheet/lcsc_datasheet_2106070033_C-K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","kmj_custom:SW_SPST_PTS810","1","","C2689510","C&K","PTS815SJM250SMTRLFS","CKN12215-1-ND"
"U1","3V3LDO","https://wmsc.lcsc.com/wmsc/upload/file/pdf/v2/lcsc/230414003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","Package_TO_SOT_SMD:SOT-23","1","","C5446","Torex Semicon","XC6206P332MR-G","893-XC6206P332MR-GCT-ND"
"U2","32Mb QSPI","https://wmsc.lcsc.com/wmsc/upload/file/pdf/v2/lcsc/221109180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","kmj_custom:Winbond_USON-8-1EP_3x2mm_P0.5mm_EP0.2x1.6mm","1","","C5258281","Zetta","ZD25WQ32CEIGR","256-W25Q32RVXHJQTRCT-ND"
"U3","LSM6DS3TR-C","https://www.lcsc.com/datasheet/lcsc_datasheet_2102261805_STM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","Package_LGA:LGA-14_3x2.5mm_P0.5mm_LayoutBorder3x4y","1","","C967633","STMicroelectronics","LSM6DS3TR-C","497-LSM6DS3TR-CTR-ND"
"U4","TPS61022","https://www.ti.com/lit/ds/symlink/tps61022.pdf","kmj_custom:Texas_RWU0007A_VQFN-7_2x2mm_P0.5mm","1","","C915088","Texas Instruments","TPS61022RWUR","296-TPS61022RWURCT-ND"
"U6","RP2040","https://wmsc.lcsc.com/wmsc/upload/file/pdf/v2/lcsc/220110160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","Package_DFN_QFN:QFN-56-1EP_7x7mm_P0.4mm_EP3.2x3.2mm","1","","C2040","Raspberry Pi","RP2040","2648-SC0914(13)CT-ND"
"X1","Simple_Addon_v2","https://wmsc.lcsc.com/wmsc/upload/file/pdf/v2/lcsc/181115153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","kmj_custom:Simple_Addon_v2-SAO-2x3","1","DNP","C168680","Amphenol ICC","75869-131LF","609-2845-ND"
"Y1","12M","https://wmsc.lcsc.com/wmsc/upload/file/pdf/v2/lcsc/240329150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","Crystal:Crystal_SMD_SeikoEpson_FA238-4Pin_3.2x2.5mm","1","","C9002","YXC Crystal Oscillators","X322512MSB4SI","XC1810CT-ND"

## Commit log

2024-09-12 spelling
2024-09-22 connected buzzer and sel nets
2024-10-02 fixed all rev0 issues
    connected buzzer and bootsel nets
    changed IMU to I2C mode
    changed IMU to the cheaper -C model
    changed all buttons to PTS815
    changed order of WS2812s so that the frame buffer can be shifted monolithically
    changed boost converter feedback network to use JLCPCB basic parts
2024-10-15 demo updates for rev1, kicad exports
2024-10-15 c sdk demo
2024-10-18 imu graphic
2024-10-22 imusand demo
2024-10-22 floppybit
